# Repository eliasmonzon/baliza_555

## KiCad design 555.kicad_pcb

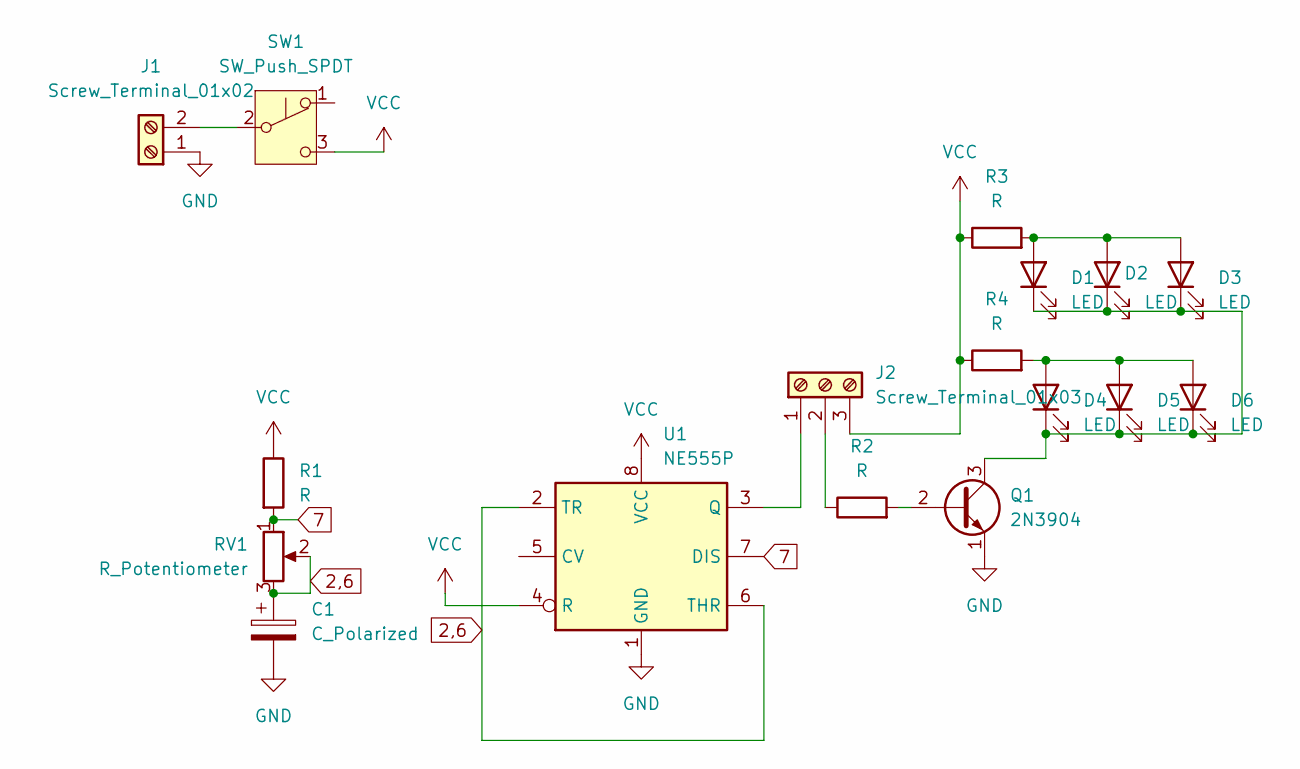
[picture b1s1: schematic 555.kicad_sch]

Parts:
C1: C_Polarized; CP_Radial_D4.0mm_P2.00mm
D1, D2, D3, D4, D5, D6: LED; LED_D5.0mm
J1: Screw_Terminal_01x02; TerminalBlock_Phoenix_MKDS-1,5-2-5.08_1x02_P5.08mm_Horizont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
J2: Screw_Terminal_01x03; TerminalBlock_Phoenix_MKDS-1,5-3_1x03_P5.00mm_Horizontal
Q1: 2N3904; TO-92_Inline
R1, R2, R3, R4: R; R_Axial_DIN0204_L3.6mm_D1.6mm_P5.08mm_Horizontal
RV1: R_Potentiometer; Potentiometer_Vishay_T73XX_Horizontal
SW1: SW_Push_SPDT; SW_Slide_SPDT_Angled_CK_OS102011MA1Q
U1: NE555P; DIP-8_W7.62mm

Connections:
2,6: C1.1, RV1.2, RV1.3, U1.2 (TR), U1.6 (THR)
7: R1.2, RV1.1, U1.7 (DIS)
GND: C1.2, J1.1, Q1.1 (E), U1.1 (GND)
unnamed: D1.2 (A), D2.2 (A), D3.2 (A), R3.2
unnamed: D1.1 (K), D2.1 (K), D3.1 (K), D4.1 (K), D5.1 (K), D6.1 (K), Q1.3 (C)
unnamed: D4.2 (A), D5.2 (A), D6.2 (A), R4.2
unnamed: J1.2, SW1.2 (B)
unnamed: J2.1, U1.3 (Q)
unnamed: J2.2, R2.1
unnamed: Q1.2 (B), R2.2
VCC: J2.3, R1.1, R3.1, R4.1, SW1.3 (C), U1.4 (R), U1.8 (VCC)

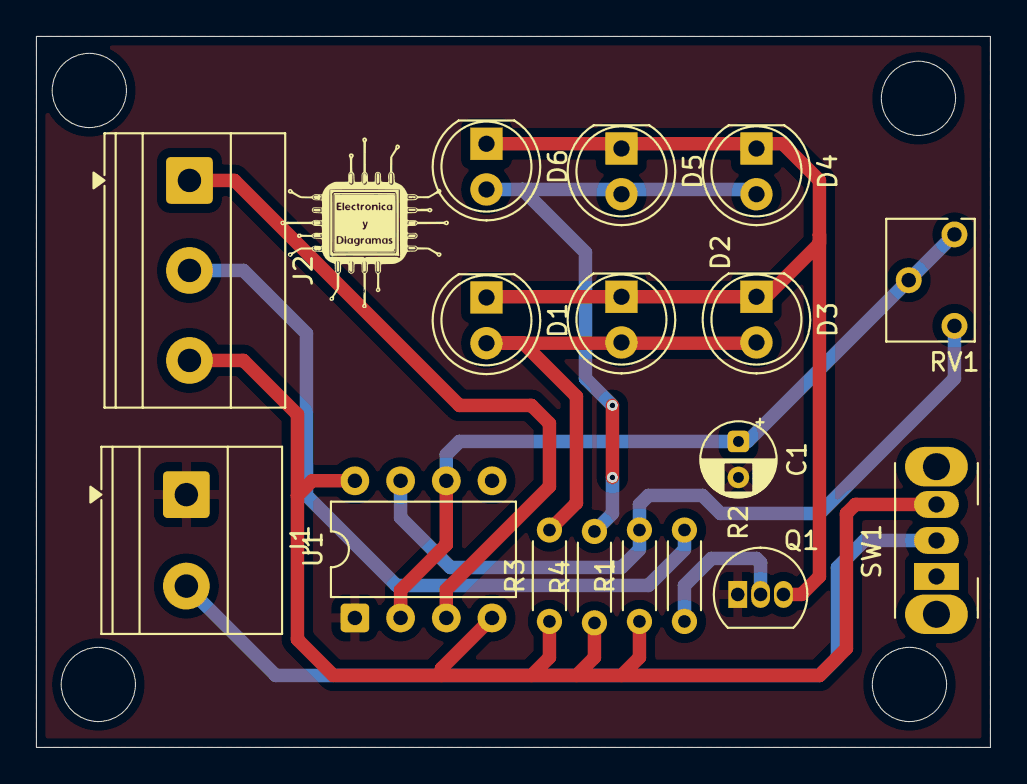
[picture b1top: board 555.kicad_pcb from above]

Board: 2 copper layers, 53.0 x 39.5 mm, 17 parts (0 on the bottom side), 11 nets.

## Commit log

2025-07-12 baliza_555
2025-07-14 modificado_pc
